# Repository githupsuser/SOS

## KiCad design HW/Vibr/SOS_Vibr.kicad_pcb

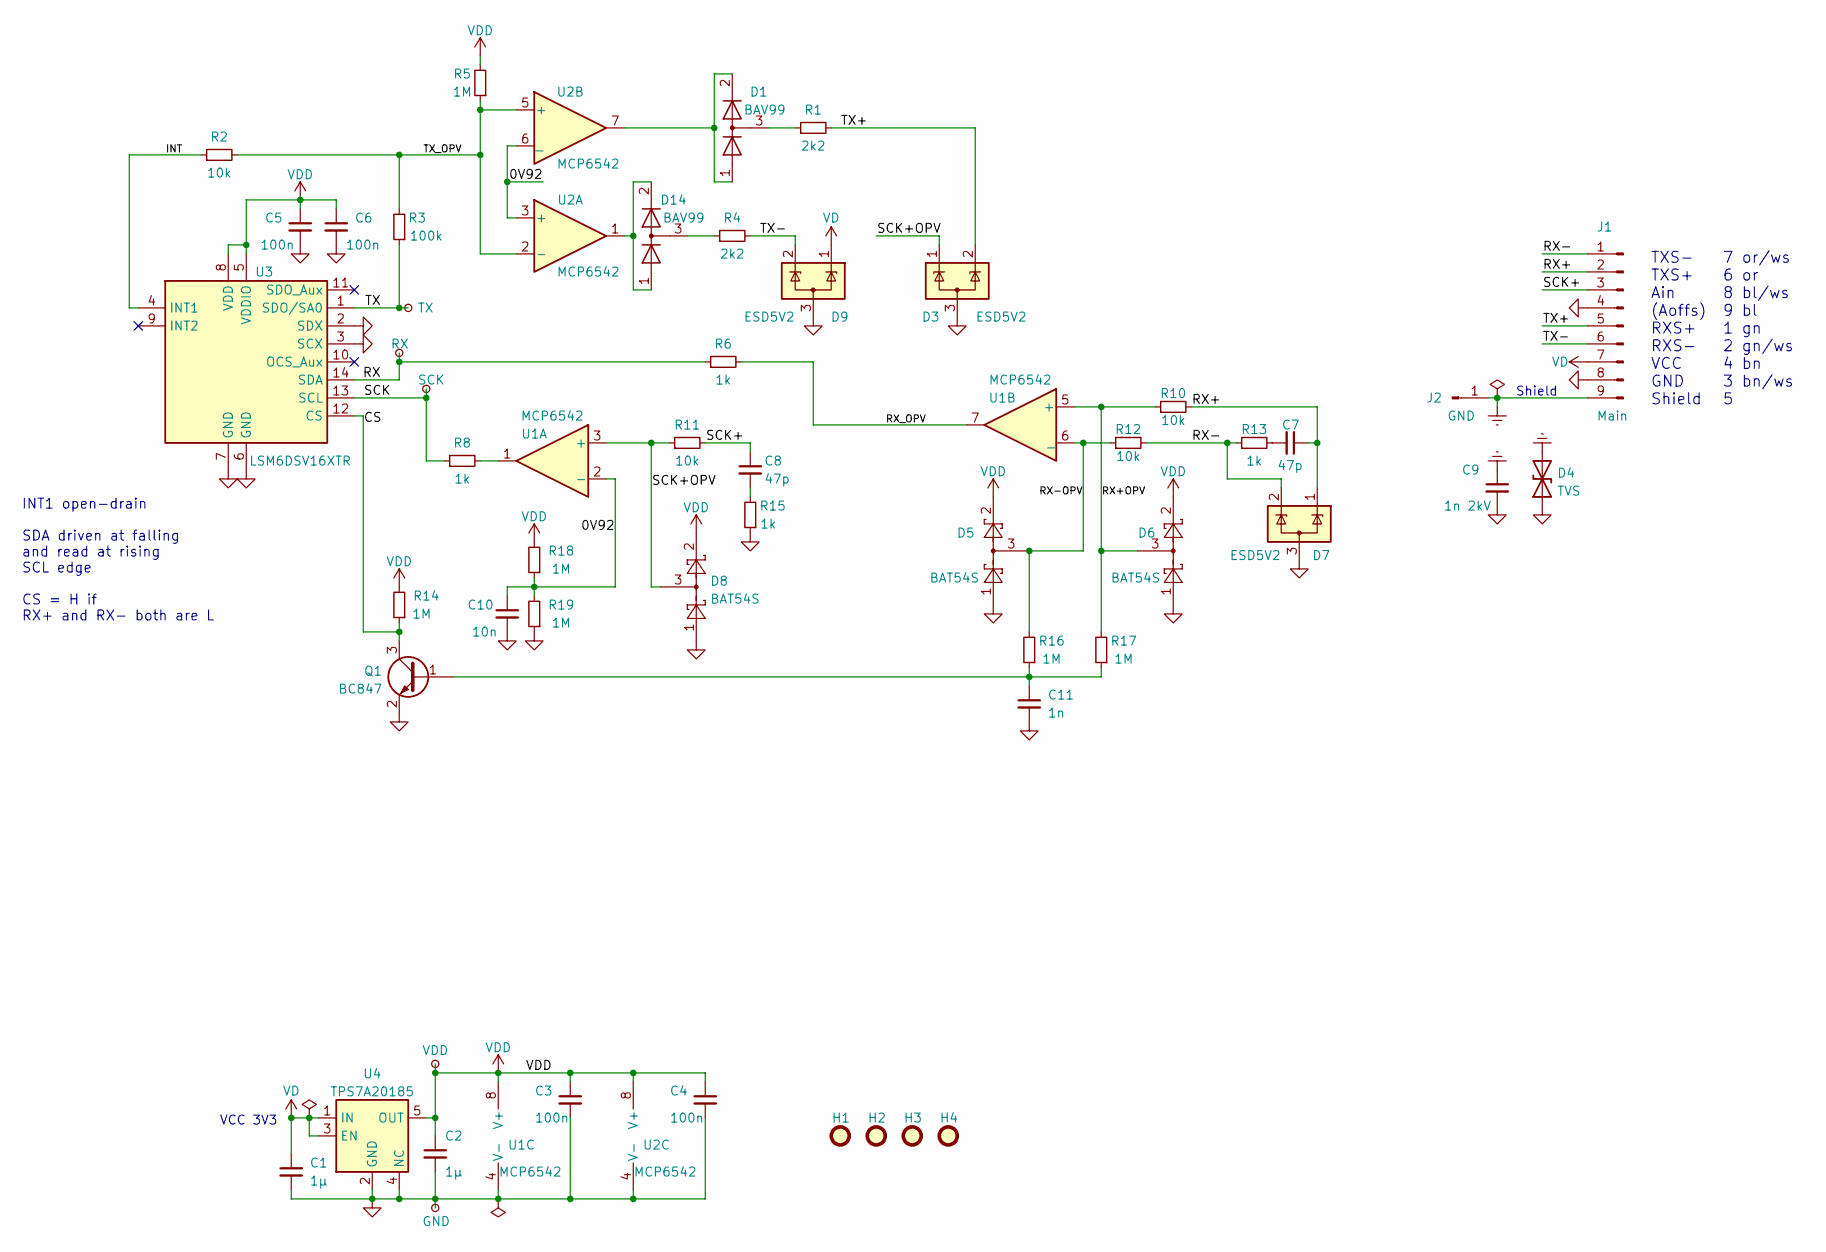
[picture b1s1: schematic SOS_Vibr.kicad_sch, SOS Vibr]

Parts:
C1, C2: 1µ; C_0805_2012Metric
C3, C4, C5, C6: 100n; C_0603_1608Metric
C7, C8: 47p; C_0603_1608Metric
C9: 1n 2kV; C_1206_3216Metric
C10: 10n; C_0603_1608Metric
C11: 1n; C_0603_1608Metric
D1, D14: BAV99; SOT-23
D3, D7, D9: ESD5V2; SOT-23
D4: TVS; D_SMA
D5, D6, D8: BAT54S; SOT-23
H1, H2, H3, H4: MountingHole; MountingHole_2.7mm_M2.5
J1: Main; PinHeader_1x09_P2.54mm_Vertical
J2: GND; SolderWire-0.75sqmm_1x01_D1.25mm_OD2.3mm
Q1: BC847; SOT-23
R1, R4: 2k2; R_0603_1608Metric
R2, R10, R11, R12: 10k; R_0603_1608Metric
R3: 100k; R_0603_1608Metric
R5, R14, R16, R17, R18, R19: 1M; R_0805_2012Metric
R6, R8, R13, R15: 1k; R_0603_1608Metric
TP1: VDD; TestPoint_THTPad_D1.0mm_Drill0.6mm
TP2: TX; TestPoint_THTPad_D1.0mm_Drill0.6mm
TP3: RX; TestPoint_THTPad_D1.0mm_Drill0.6mm
TP4: SCK; TestPoint_THTPad_D1.0mm_Drill0.6mm
TP5: GND; TestPoint_THTPad_D1.0mm_Drill0.6mm
U1, U2: MCP6542; SOIC-8_3.9x4.9mm_P1.27mm
U3: LSM6DSV16XTR; LGA-14_3x2.5mm_P0.5mm_LayoutBorder3x4y
U4: TPS7A20185; SOT-23-5

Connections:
/0V92: C10.1, R18.1, R19.2, U1.2 (-), U2.3 (+), U2.6 (_)
/CS: Q1.3 (C), R14.1, U3.12 (CS)
/INT: R2.1, U3.4 (INT1)
/RX: R6.1, TP3.1, U3.14 (SDA)
/RX+: C7.1, D7.1 (K), J1.2, R10.2
/RX+OPV: D6.3, R10.1, R17.2, U1.5 (+)
/RX-: D7.2 (K), J1.1, R12.2, R13.1
/RX-OPV: D5.3, R12.1, R16.2, U1.6 (_)
/RX_OPV: R6.2, U1.7
/SCK: R8.1, TP4.1, U3.13 (SCL)
/SCK+: C8.1, J1.3, R11.2
/SCK+OPV: D3.1 (K), D8.3, R11.1, U1.3 (+)
/TX: R3.1, TP2.1, U3.1 (SDO/SA0)
/TX+: D3.2 (K), J1.5, R1.2
/TX-: D9.2 (K), J1.6, R4.2
/TX_OPV: R2.2, R3.2, R5.1, U2.2 (-), U2.5 (+)
Earth: C9.1, D4.2 (A2), J1.9, J2.1
GNDA: C1.2, C2.2, C3.2, C4.2, C5.2, C6.2, C9.2, C10.2, C11.2, D3.3 (A), D4.1 (A1), D5.1, D6.1, D7.3 (A), D8.1, D9.3 (A), J1.4, J1.8, Q1.2 (E), R15.1, R19.1, TP5.1, U1.4 (V-), U2.4 (V-), U3.2 (SDX), U3.3 (SCX), U3.6 (GND), U3.7 (GND), U4.2 (GND), U4.4 (NC)
unnamed: C7.2, R13.2
unnamed: C8.2, R15.2
unnamed: C11.1, Q1.1 (B), R16.1, R17.1
unnamed: D1.1 (K), D1.2 (A), U2.7
unnamed: D1.3 (K), R1.1
unnamed: D14.1 (K), D14.2 (A), U2.1
unnamed: D14.3 (K), R4.1
unnamed: R8.2, U1.1
VD: C1.1, D9.1 (K), J1.7, U4.1 (IN), U4.3 (EN)
VDD: C2.1, C3.1, C4.1, C5.1, C6.1, D5.2, D6.2, D8.2, R5.2, R14.2, R18.2, TP1.1, U1.8 (V+), U2.8 (V+), U3.5 (VDDIO), U3.8 (VDD), U4.5 (OUT)

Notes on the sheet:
VCC 3V3
TXS- TXS+ Ain (Aoffs) RXS+ RXS- VCC GND Shield
7 or/ws 6 or 8 bl/ws 9 bl 1 gn 2 gn/ws 4 bn 3 bn/ws 5
INT1 open-drain SDA driven at falling and read at rising SCL edge CS = H if RX+ and RX- both are L
Shield

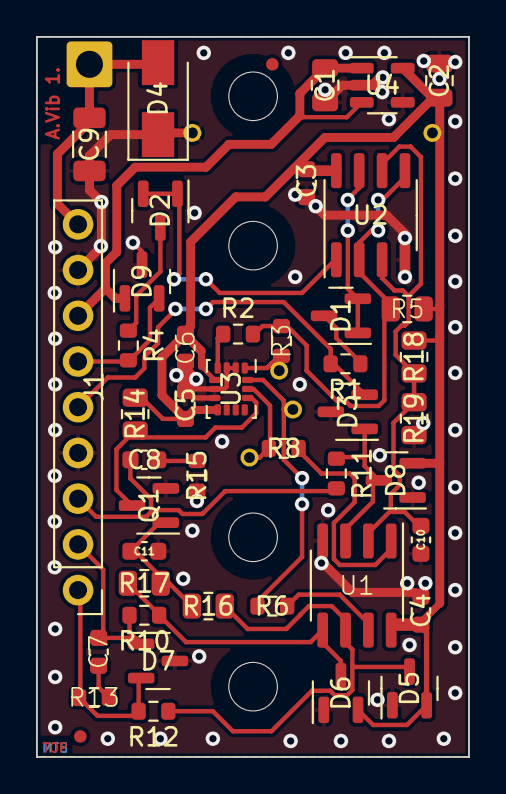
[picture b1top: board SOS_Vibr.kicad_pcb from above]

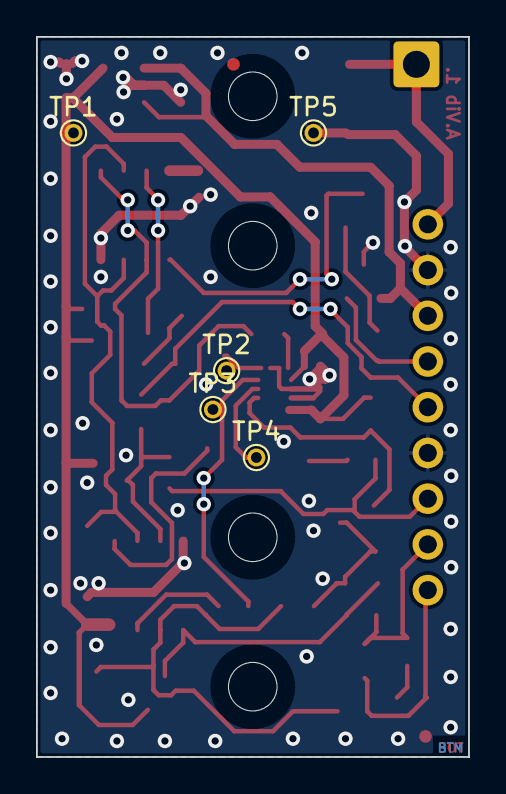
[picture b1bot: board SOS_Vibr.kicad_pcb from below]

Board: 2 copper layers, 24.0 x 40.0 mm, 53 parts (5 on the bottom side), 28 nets.

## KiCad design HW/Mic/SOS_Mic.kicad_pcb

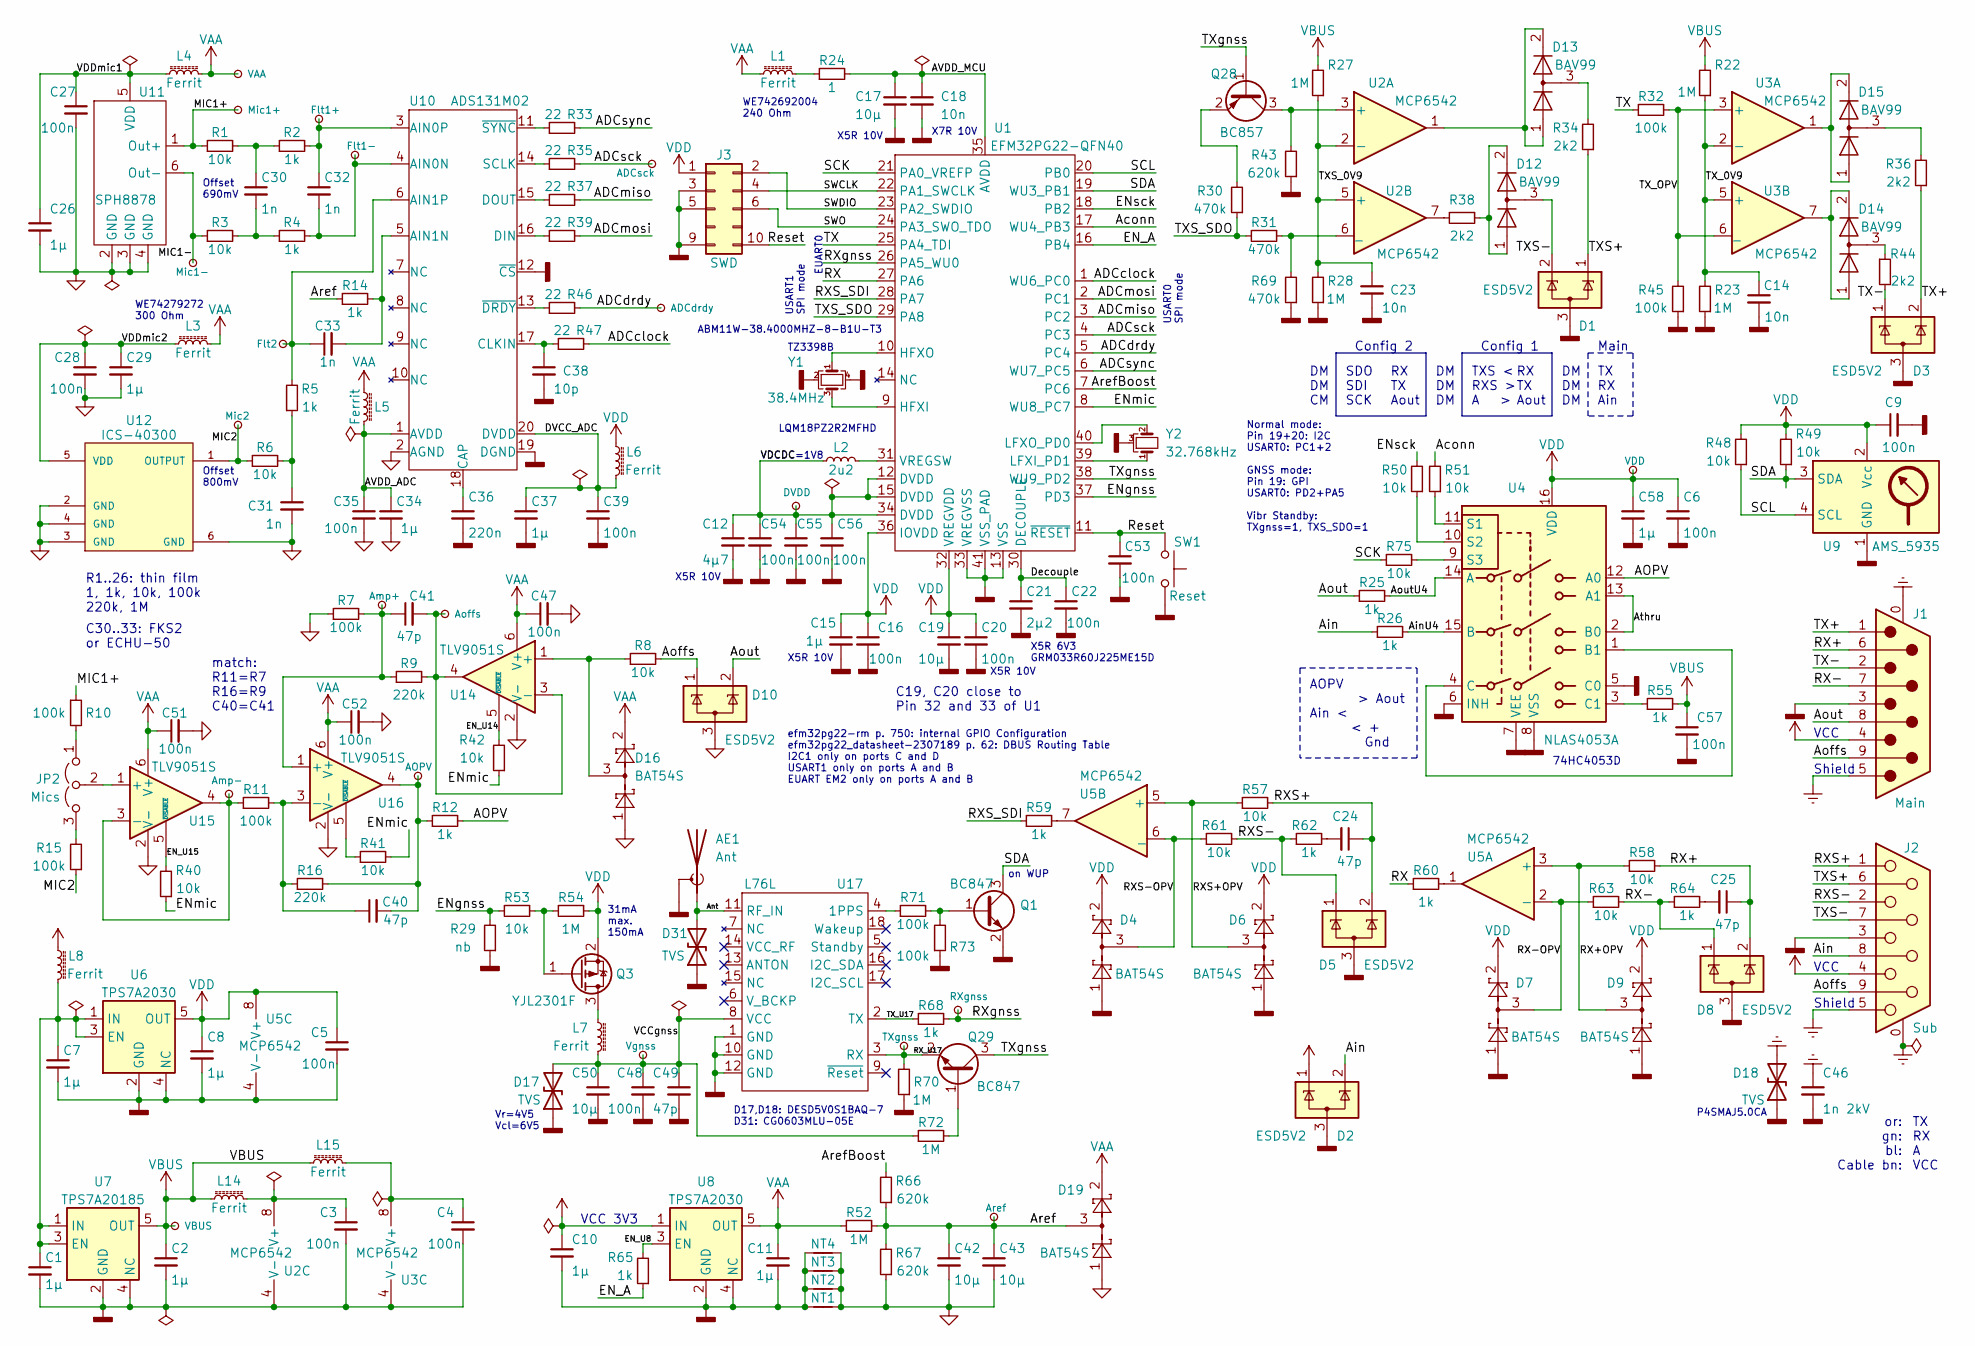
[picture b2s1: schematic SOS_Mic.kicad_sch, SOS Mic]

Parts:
AE1: Ant; IPEX_20279-001E-03
C1, C2, C7, C8, C10, C11, C15, C26, C29, C34, C37, C58: 1µ; C_0805_2012Metric
C3, C4, C5, C6, C9, C16, C20, C22, C27, C28, C35, C39, C47, C48, C51, C52, C53, C54, C55, C56, C57: 100n; C_0603_1608Metric
C12: 4µ7; C_0805_2012Metric
C14, C18, C23: 10n; C_0603_1608Metric
C17, C19, C42, C43, C50: 10µ; C_1206_3216Metric
C21: 2µ2; C_0805_2012Metric
C24, C25, C40, C41, C49: 47p; C_0603_1608Metric
C30, C31, C32, C33: 1n; C_0805_2012Metric
C36: 220n; C_0603_1608Metric
C38: 10p; C_0603_1608Metric
C46: 1n 2kV; C_1206_3216Metric
D1, D2, D3, D5, D8, D10: ESD5V2; SOT-23
D4, D6, D7, D9, D16, D19: BAT54S; SOT-23
D12, D13, D14, D15: BAV99; SOT-23
D17, D18: TVS; D_SMA
D31: TVS; D_0603_1608Metric
J1: Main; DSUB-9_Male_Horizontal_P2.77x2.84mm_EdgePinOffset7.70mm_Hou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
J2: Sub; DSUB-9_Female_Horizontal_P2.77x2.84mm_EdgePinOffset7.70mm_H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
J3: SWD; PinHeader_2x05_P1.27mm_Vertical
JP2: Mics; PinHeader_1x03_P2.54mm_Vertical
L1, L3, L4, L5, L6, L7, L8, L14, L15: Ferrit; L_0805_2012Metric
L2: 2u2; L_0805_2012Metric
NT1, NT2, NT3, NT4: Conn; Bridged2Bar_Pad1.0x1.5mm
Q1, Q29: BC847; SOT-23
Q3: YJL2301F; SOT-23-3
Q28: BC857; SOT-23
R1, R3, R6, R8, R40, R41, R42, R48, R49, R50, R51, R53, R57, R58, R61, R63, R75: 10k; R_0603_1608Metric
R2, R4, R5, R12, R14, R25, R26, R55, R59, R60, R62, R64, R65, R68: 1k; R_0603_1608Metric
R7, R10, R11, R15: 100k; R_0805_2012Metric
R9, R16: 220k; R_0805_2012Metric
R22, R23, R27, R28, R52, R54, R70, R72: 1M; R_0805_2012Metric
R24: 1; R_0805_2012Metric
R29: nb; R_0603_1608Metric
R30, R31, R69: 470k; R_0603_1608Metric
R32, R45, R71, R73: 100k; R_0603_1608Metric_Pad0.98x0.95mm_HandSolder
R33, R35, R37, R39, R46, R47: 22; R_0603_1608Metric
R34, R36, R38, R44: 2k2; R_0805_2012Metric
R43, R66, R67: 620k; R_0603_1608Metric
SW1: Reset; SW_Push_1P1T_NO_Vertical_Wuerth_434133025816
TP1: VBUS; TestPoint_THTPad_D1.0mm_Drill0.6mm
TP2: VDD; TestPoint_THTPad_D1.0mm_Drill0.6mm
TP3: DVDD; TestPoint_THTPad_D1.0mm_Drill0.6mm
TP4: Mic1-; TestPoint_THTPad_D1.0mm_Drill0.6mm
TP5: VAA; TestPoint_THTPad_D1.0mm_Drill0.6mm
TP6: Mic1+; TestPoint_THTPad_D1.0mm_Drill0.6mm
TP7: Mic2; TestPoint_THTPad_D1.0mm_Drill0.6mm
TP8: Flt2; TestPoint_THTPad_D1.0mm_Drill0.6mm
TP9: Flt1+; TestPoint_THTPad_D1.0mm_Drill0.6mm
TP10: Flt1-; TestPoint_THTPad_D1.0mm_Drill0.6mm
TP11: Amp+; TestPoint_THTPad_D1.0mm_Drill0.6mm
TP12: Aoffs; TestPoint_THTPad_D1.0mm_Drill0.6mm
TP14: Aref; TestPoint_THTPad_D1.0mm_Drill0.6mm
TP15: Amp-; TestPoint_THTPad_D1.0mm_Drill0.6mm
TP16: AOPV; TestPoint_THTPad_D1.0mm_Drill0.6mm
TP18: Vgnss; TestPoint_THTPad_D1.0mm_Drill0.6mm
TP19: ADCsck; TestPoint_THTPad_D1.0mm_Drill0.6mm
TP20: ADCdrdy; TestPoint_THTPad_D1.0mm_Drill0.6mm
TP21: RXgnss; TestPoint_THTPad_D1.0mm_Drill0.6mm
TP22: TXgnss; TestPoint_THTPad_D1.0mm_Drill0.6mm
U1: EFM32PG22-QFN40; QFN-40-1EP_5x5mm_P0.4mm_EP3.8x3.8mm
U2, U3, U5: MCP6542; SOIC-8_3.9x4.9mm_P1.27mm
U4: NLAS4053A; SOIC-16_3.9x9.9mm_P1.27mm
U6, U8: TPS7A2030; SOT-23-5
U7: TPS7A20185; SOT-23-5
U9: AMS_5935; DIP-8_W7.62mm_L15.25mm
U10: ADS131M02; TSSOP-20_4.4x6.5mm_P0.65mm
U11: SPH8878; Knowles_LGA-6_3.5x2.65mm
U12: ICS-40300; MIC_ICS-40300
U14, U15, U16: TLV9051S; SOT-23-6
U17: L76L; XCVR_L76-L
Y1: 38.4MHz; Crystal_SMD_2520-4Pin_2.5x2.0mm
Y2: 32.768kHz; Crystal_C26-LF_D2.1mm_L6.5mm_Horizontal_1EP_style1

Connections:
/ADCclock: R47.2, U1.1 (WU6_PC0)
/ADCdrdy: R46.2, TP20.1, U1.5 (PC4)
/ADCmiso: R37.2, U1.3 (PC2)
/ADCmosi: R39.2, U1.2 (PC1)
/ADCsck: R35.2, TP19.1, U1.4 (PC3)
/ADCsync: R33.2, U1.6 (WU7_PC5)
/AOPV: R12.2, U4.12 (A0)
/AVDD_ADC: C34.1, C35.1, L5.2, U10.1 (AVDD)
/AVDD_MCU: C17.1, C18.1, R24.2, U1.35 (AVDD)
/Aconn: R51.2, U1.17 (WU4_PB3)
/Ain: D2.2 (K), J2.8, R26.1
/AinU4: R26.2, U4.15 (B)
/Ant: AE1.1 (A), D31.2 (A2), U17.11 (RF_IN)
/Aoffs: D10.1 (K), J1.9, J2.9, R8.2
/Aout: D10.2 (K), J1.8, R25.1
/AoutU4: R25.2, U4.14 (A)
/Aref: C42.1, C43.1, D19.3, R14.1, R52.2, R66.1, R67.2, TP14.1
/ArefBoost: R66.2, U1.7 (PC6)
/Athru: U4.2 (B0), U4.13 (A1)
/DVCC_ADC: C37.1, C39.1, L6.2, U10.20 (DVDD)
/Decouple: C21.1, C22.1, U1.30 (DECOUPLE)
/EN_A: R65.1, U1.16 (PB4)
/EN_U8: R65.2, U8.3 (EN)
/EN_U14: R42.2, U14.5 (~DISABLE)
/EN_U15: R40.2, U15.5 (~DISABLE)
/ENgnss: R29.2, R53.2, U1.37 (PD3)
/ENmic: R40.1, R41.2, R42.1, U1.8 (WU8_PC7)
/ENsck: R50.2, U1.18 (PB2)
/MIC1+: R1.1, R10.1, TP6.1, U11.1 (Out+)
/MIC1-: R3.1, TP4.1, U11.6 (Out-)
/MIC2: R6.1, R15.1, TP7.1, U12.1 (OUTPUT)
/RX: R60.1, U1.27 (PA6)
/RX+: C25.1, D8.2 (K), J1.6, R58.2
/RX+OPV: D9.3, R58.1, U5.3 (+)
/RX-: D8.1 (K), J1.7, R63.2, R64.1
/RX-OPV: D7.3, R63.1, U5.2 (-)
/RXS+: C24.1, D5.2 (K), J2.1, R57.2
/RXS+OPV: D6.3, R57.1, U5.5 (+)
/RXS-: D5.1 (K), J2.2, R61.2, R62.1
/RXS-OPV: D4.3, R61.1, U5.6 (_)
/RXS_SDI: R59.1, U1.28 (PA7)
/RX_U17: Q29.2 (E), R70.2, TP22.1, U17.3 (RX)
/RXgnss: R68.2, TP21.1, U1.26 (PA5_WU0)
/Reset: C53.1, J3.10, SW1.2, U1.11 (~RESET)
/SCK: R75.1, U1.21 (PA0_VREFP)
/SCL: R48.1, U1.20 (PB0), U9.4 (SCL)
/SDA: Q1.3 (C), R49.1, U1.19 (WU3_PB1), U9.3 (SDA)
/SWCLK: J3.4, U1.22 (PA1_SWCLK)
/SWDIO: J3.2, U1.23 (PA2_SWDIO)
/SWO: J3.6, U1.24 (PA3_SWO_TDO)
/TX: R32.1, U1.25 (PA4_TDI)
/TX+: D3.2 (K), J1.1, R36.1
/TX-: D3.1 (K), J1.2, R44.2
/TXS+: D1.1 (K), J2.6, R34.1
/TXS-: D1.2 (K), D12.3 (K), J2.7
/TXS_0V9: C23.1, R27.1, R28.2, U2.2 (-), U2.5 (+)
/TXS_SDO: R30.1, R31.2, U1.29 (PA8)
/TX_0V9: C14.1, R22.1, R23.2, U3.2 (-), U3.5 (+)
/TX_OPV: R32.2, R45.2, U3.3 (+), U3.6 (_)
/TX_U17: R68.1, U17.2 (TX)
/TXgnss: Q28.1 (B), Q29.3 (C), U1.38 (WU9_PD2)
/VCCgnss: C48.1, C49.1, C50.1, D17.2 (A2), L7.2, R72.1, TP18.1, U17.8 (VCC)
/VDCDC: C12.1, C54.1, C55.1, C56.1, L2.1, TP3.1, U1.12 (DVDD), U1.15 (DVDD), U1.34 (DVDD)
/VDDmic1: C26.1, C27.1, L4.1, U11.5 (VDD)
/VDDmic2: C28.1, C29.1, L3.1, U12.5 (VDD)
Earth: C46.1, D18.2 (A2), J1.0 (PAD), J1.5, J2.0 (PAD), J2.5
GNDA: C26.2, C27.2, C28.2, C29.2, C31.2, C34.2, C35.2, C42.2, C43.2, C47.2, C51.2, C52.2, D10.3 (A), D16.1, D19.1, NT1.1, NT2.1, NT3.1, NT4.1, R7.1, R67.1, U10.2 (AGND), U11.2 (GND), U11.3 (GND), U11.4 (GND), U12.2 (GND), U12.3 (GND), U12.4 (GND), U12.6 (GND), U14.2 (V-), U15.2 (V-), U16.2 (V-)
GNDD: AE1.2 (Shield), AE1.3 (Shield), C1.2, C2.2, C3.2, C4.2, C5.2, C6.2, C7.2, C8.2, C9.2, C10.2, C11.2, C12.2, C14.2, C15.2, C16.2, C17.2, C18.2, C19.2, C20.2, C21.2, C22.2, C23.2, C36.2, C37.2, C38.2, C39.2, C46.2, C48.2, C49.2, C50.2, C53.2, C54.2, C55.2, C56.2, C57.2, C58.2, D1.3 (A), D2.3 (A), D3.3 (A), D4.1, D5.3 (A), D6.1, D7.1, D8.3 (A), D9.1, D17.1 (A1), D18.1 (A1), D31.1 (A1), J1.3, J2.3, J3.3, J3.5, J3.9, NT1.2, NT2.2, NT3.2, NT4.2, Q1.2 (E), R23.1, R28.1, R29.1, R43.1, R45.1, R69.1, R70.1, R73.1, SW1.1, U1.13 (VSS), U1.33 (VREGVSS), U1.41 (VSS_PAD), U2.4 (V-), U3.4 (V-), U4.5 (C0), U4.6 (INH), U4.7 (VEE), U4.8 (VSS), U5.4 (V-), U6.2 (GND), U6.4 (NC), U7.2 (GND), U7.4 (NC), U8.2 (GND), U8.4 (NC), U9.1 (GND), U10.12 (~CS), U10.19 (DGND), U17.1 (GND), U17.10 (GND), U17.12 (GND), Y1.2, Y1.4, Y2.3
unnamed: C1.1, C7.1, L8.2, U6.1 (IN), U6.3 (EN), U7.1 (IN), U7.3 (EN)
unnamed: C3.1, L14.2, U2.8 (V+)
unnamed: C4.1, L15.2, U3.8 (V+)
unnamed: C24.2, R62.2
unnamed: C25.2, R64.2
unnamed: C30.1, R1.2, R2.1
unnamed: C30.2, R3.2, R4.1
unnamed: C31.1, R5.1, R6.2
unnamed: C32.1, R2.2, TP9.1, U10.3 (AIN0P)
unnamed: C32.2, R4.2, TP10.1, U10.4 (AIN0N)
unnamed: C33.1, R5.2, TP8.1, U10.6 (AIN1P)
unnamed: C33.2, R14.2, U10.5 (AIN1N)
unnamed: C36.1, U10.18 (CAP)
unnamed: C38.1, R47.1, U10.17 (CLKIN)
unnamed: C40.1, R11.2, R16.1, U16.3 (-)
unnamed: C40.2, R12.1, R16.2, TP16.1, U16.4
unnamed: C41.1, R7.2, R9.1, TP11.1, U16.1 (+)
unnamed: C41.2, R9.2, TP12.1, U14.3 (-), U14.4
unnamed: D12.1 (K), D12.2 (A), R38.1
unnamed: D13.1 (K), D13.2 (A), U2.1
unnamed: D13.3 (K), R34.2
unnamed: D14.1 (K), D14.2 (A), U3.7
unnamed: D14.3 (K), R44.1
unnamed: D15.1 (K), D15.2 (A), U3.1
unnamed: D15.3 (K), R36.2
unnamed: D16.3, R8.1, U14.1 (+)
unnamed: JP2.1 (A), R10.2
unnamed: JP2.2 (C), U15.1 (+)
unnamed: JP2.3 (B), R15.2
unnamed: L1.2, R24.1
unnamed: L2.2, U1.31 (VREGSW)
unnamed: L7.1, Q3.3 (D)
unnamed: Q1.1 (B), R71.2, R73.2
unnamed: Q3.1 (G), R53.1, R54.2
unnamed: Q28.2 (E), R30.2
unnamed: Q28.3 (C), R43.2, U2.3 (+)
unnamed: Q29.1 (B), R72.2
unnamed: R11.1, TP15.1, U15.3 (-), U15.4
unnamed: R31.1, R69.2, U2.6 (_)
unnamed: R33.1, U10.11 (~SYNC)
unnamed: R35.1, U10.14 (SCLK)
unnamed: R37.1, U10.15 (DOUT)
unnamed: R38.2, U2.7
unnamed: R39.1, U10.16 (DIN)
unnamed: R41.1, U16.5 (~DISABLE)
unnamed: R46.1, U10.13 (~DRDY)
unnamed: R50.1, U4.10 (S2)
unnamed: R51.1, U4.11 (S1)
unnamed: R55.1, U4.3 (C1)
unnamed: R59.2, U5.7
unnamed: R60.2, U5.1
unnamed: R71.1, U17.4 (1PPS)
unnamed: R75.2, U4.9 (S3)
unnamed: U1.9 (HFXI), Y1.3
unnamed: U1.10 (HFXO), Y1.1
unnamed: U1.39 (LFXI_PD1), Y2.1
unnamed: U1.40 (LFXO_PD0), Y2.2
unnamed: U4.1 (B1), U4.4 (C)
VAA: C11.1, C47.1, C51.1, C52.1, D16.2, D19.2, L1.1, L3.2, L4.2, L5.1, R52.1, TP5.1, U8.5 (OUT), U14.6 (V+), U15.6 (V+), U16.6 (V+)
VBUS: C2.1, C57.1, L14.1, L15.1, R22.2, R27.2, R55.2, TP1.1, U7.5 (OUT)
VDD: C5.1, C6.1, C8.1, C9.1, C15.1, C16.1, C19.1, C20.1, C58.1, D4.2, D6.2, D7.2, D9.2, J3.1, L6.1, Q3.2 (S), R48.2, R49.2, R54.1, TP2.1, U1.32 (VREGVDD), U1.36 (IOVDD), U4.16 (VDD), U5.8 (V+), U6.5 (OUT), U9.2 (Vcc)
VDDA: C10.1, D2.1 (K), J1.4, J2.4, L8.1, U8.1 (IN)

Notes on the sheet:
VCC
X5R 10V
C19, C20 close to Pin 32 and 33 of U1
Shield
VCC 3V3
EUART0
D17,D18: DESD5V0S1BAQ-7 D31: CG0603MLU-05E
SDO SDI SCK
DM DM DM
RX TX Aout
X7R 10V
31mA max. 150mA
match: R11=R7 R16=R9 C40=C41
R1..26: thin film 1, 1k, 10k, 100k 220k, 1M
efm32pg22-rm p. 750: internal GPIO Configuration efm32pg22_datasheet-2307189 p. 62: DBUS Routing Table I2C1 only on ports C and D USART1 only on ports A and B EUART EM2 only on ports A and B
DM DM CM
ABM11W-38.4000MHZ-8-B1U-T3
Vr=4V5 Vcl=6V5
TX RX Ain
AOPV > Aout Ain < < + Gnd
WE74279272 300 Ohm
Config 1
TX RX A VCC
Main
74HC4053D
on WUP
P4SMAJ5.0CA
Normal mode: Pin 19+20: I2C USART0: PC1+2 GNSS mode: Pin 19: GPI USART0: PD2+PA5 Vibr Standby: TXgnss=1, TXS_SDO=1
C30..33: FKS2 or ECHU-50
WE742692004 240 Ohm
X5R 6V3 GRM033R60J225ME15D
USART0 SPI mode
Offset 690mV
TZ3398B
TXS < RXS > A >
Config 2
Offset 800mV
USART1 SPI mode
LQM18PZ2R2MFHD
or: gn: bl: Cable bn:

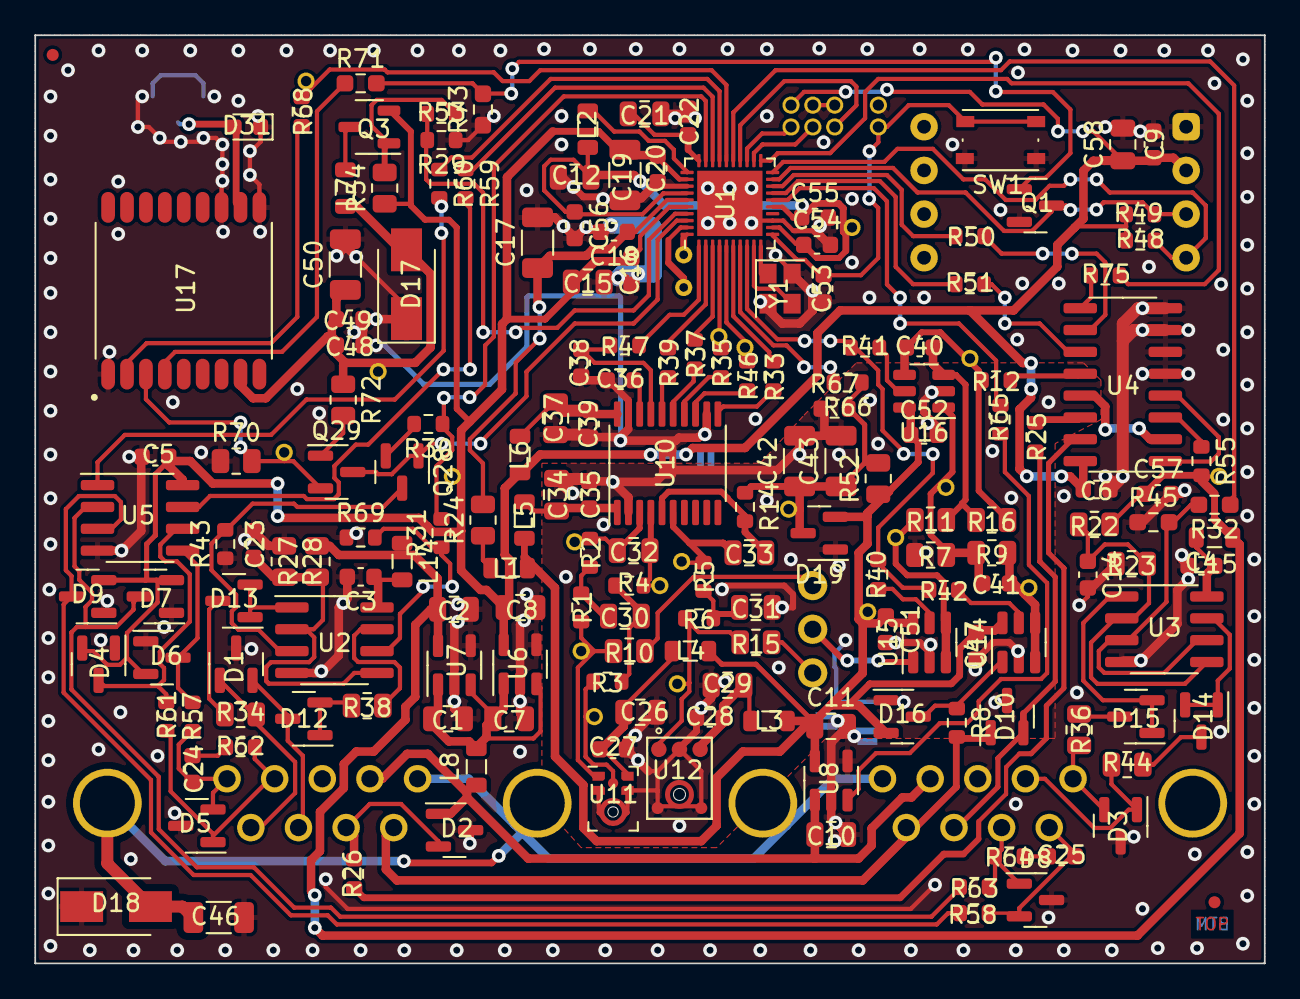
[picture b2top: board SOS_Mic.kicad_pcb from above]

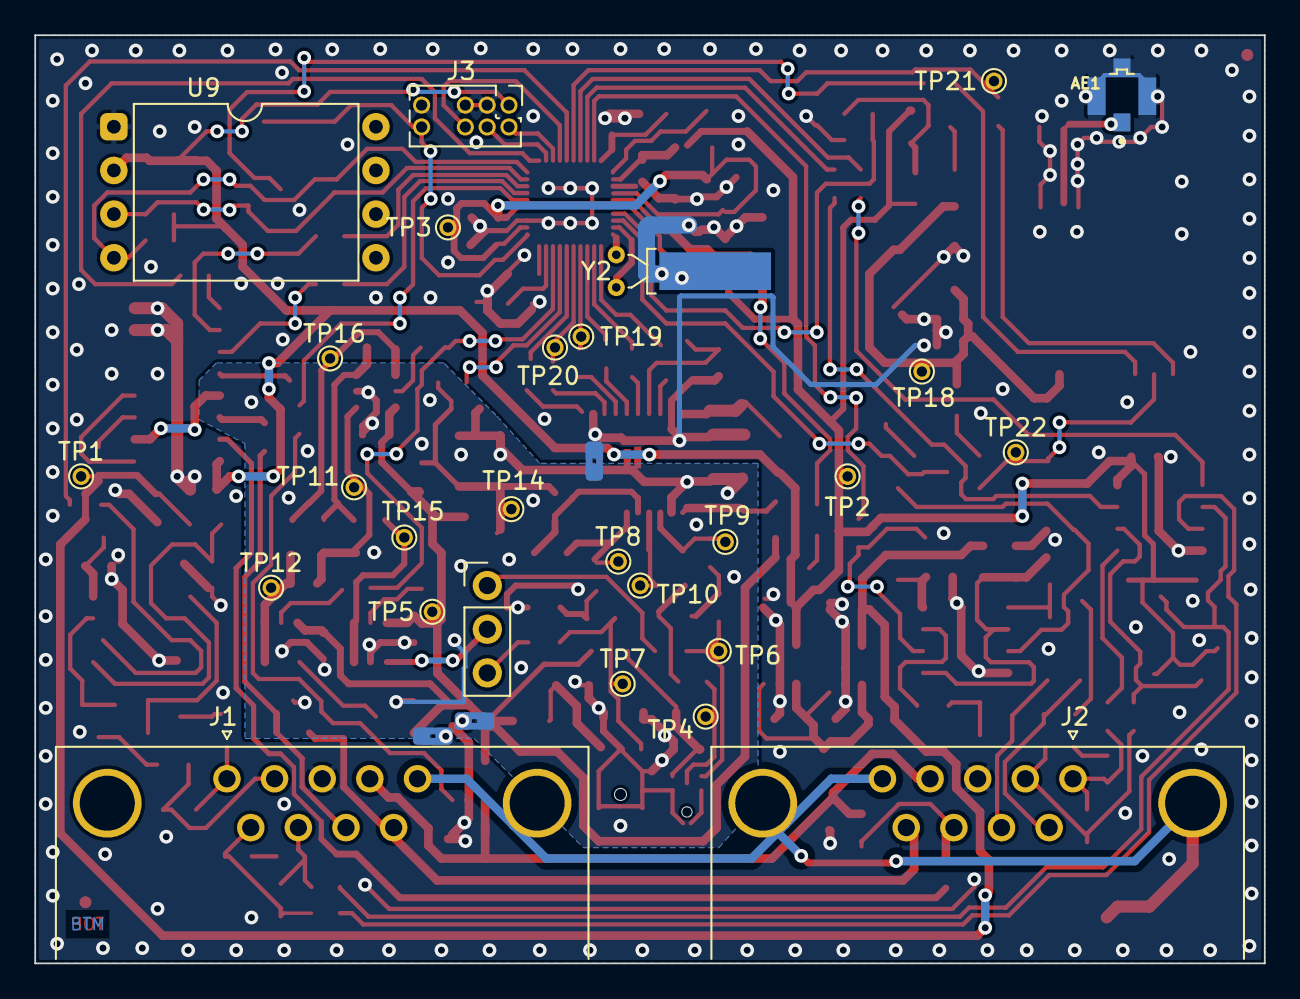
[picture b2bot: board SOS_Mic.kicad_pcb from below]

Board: 2 copper layers, 71.5 x 54.0 mm, 203 parts (30 on the bottom side), 130 nets.

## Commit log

2024-10-31 Initial doc files
2024-11-08 HW added
2024-11-08 doc updated

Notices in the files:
HW/Mic/SOS_Mic.kicad_sch:
CC BY 4.0
